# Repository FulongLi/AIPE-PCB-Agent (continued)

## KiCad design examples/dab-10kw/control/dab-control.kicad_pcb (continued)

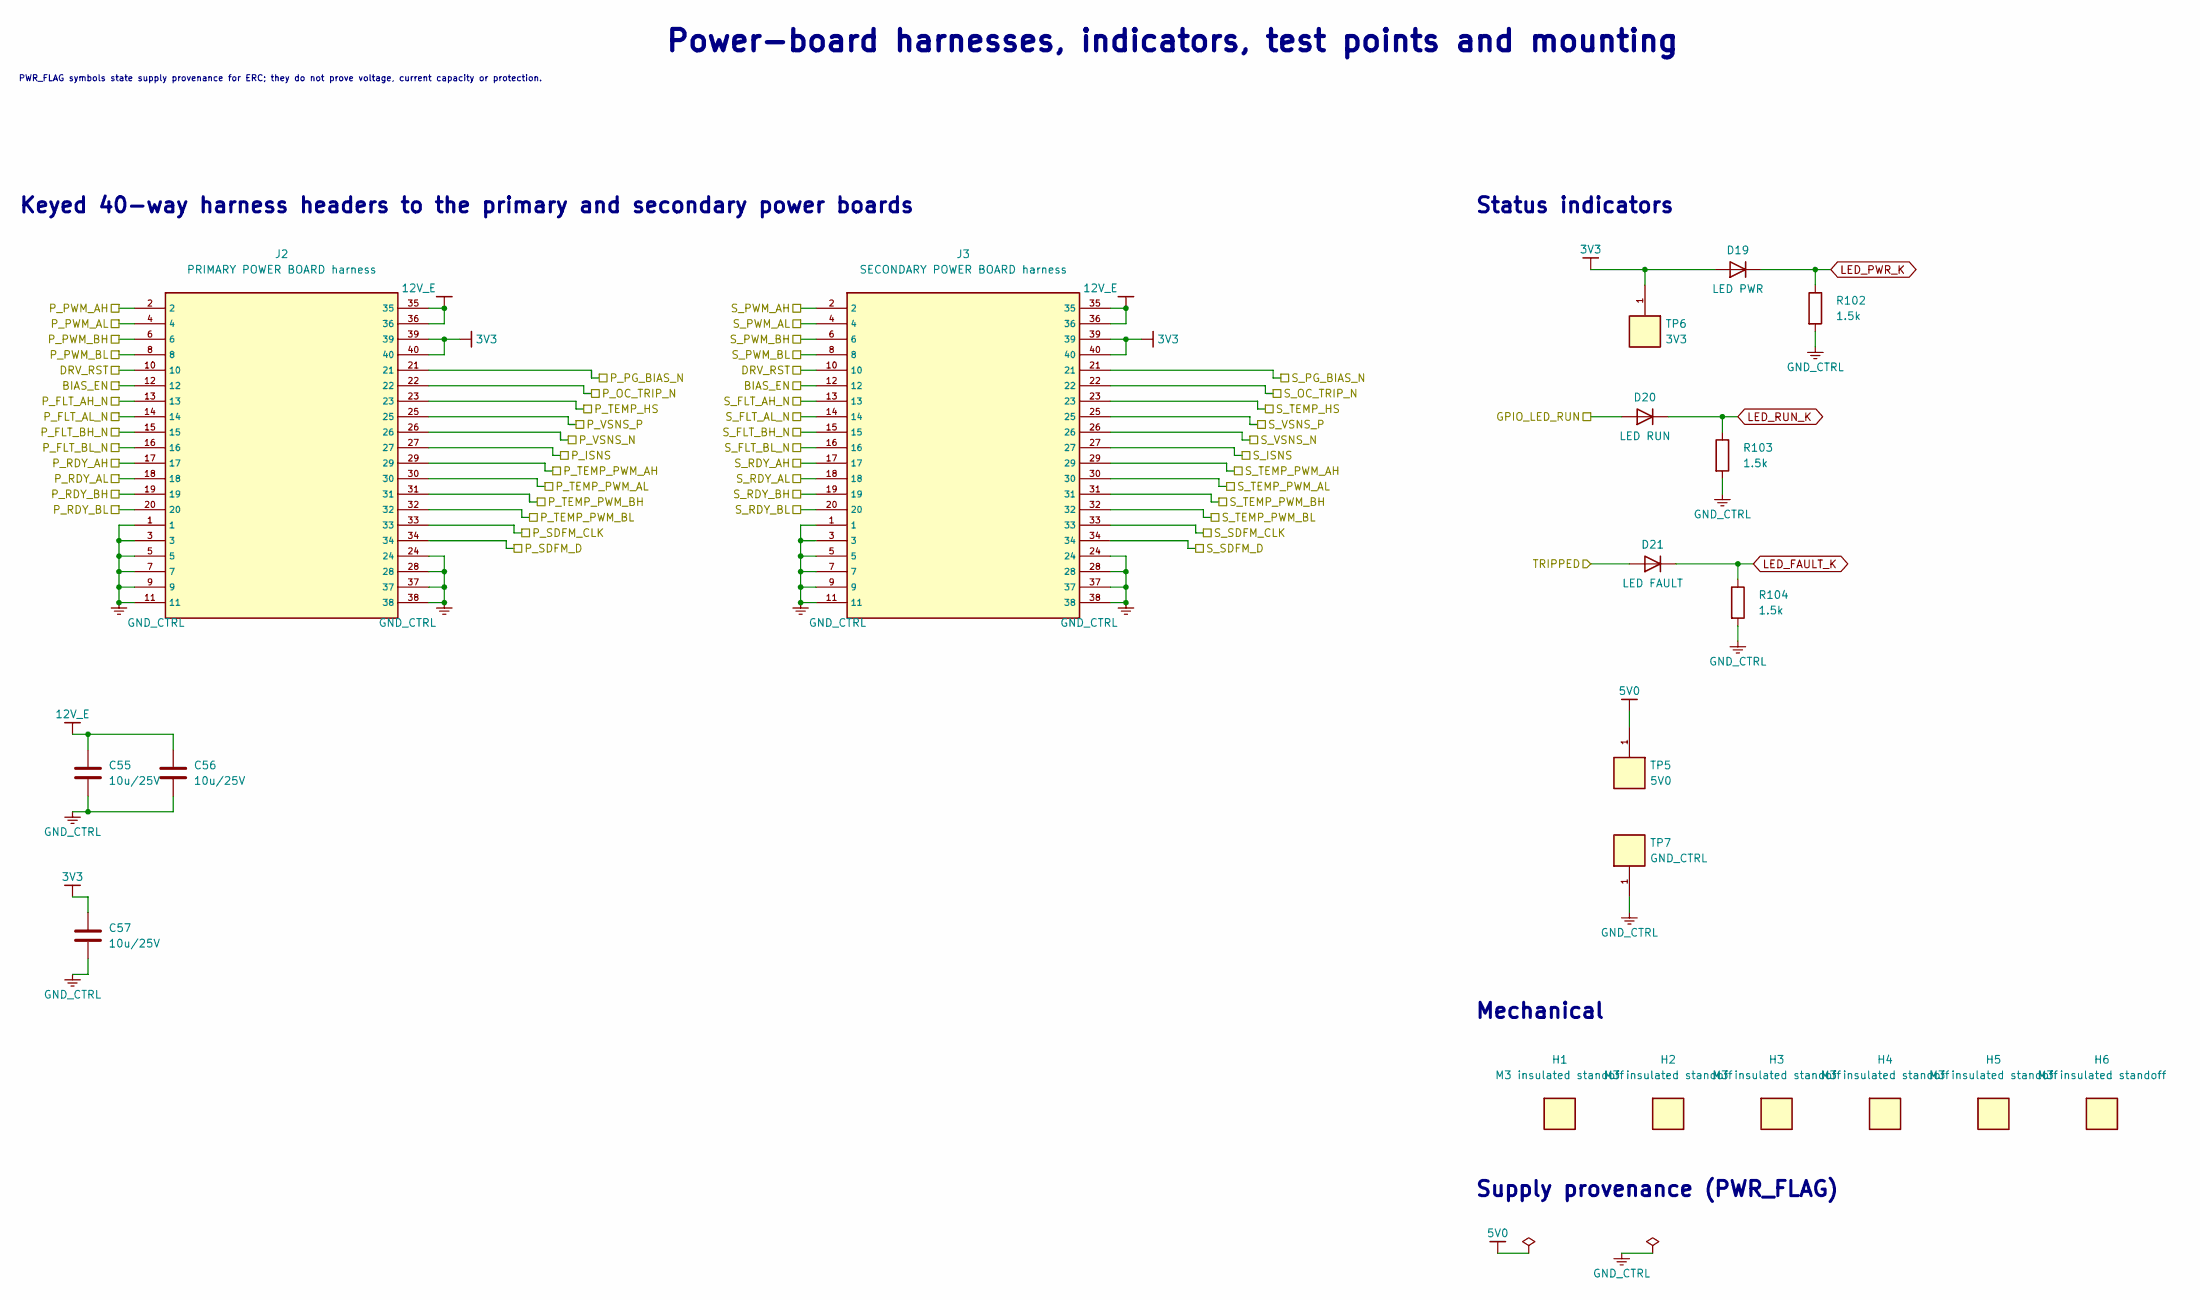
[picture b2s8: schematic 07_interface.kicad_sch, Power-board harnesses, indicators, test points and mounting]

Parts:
C55, C56, C57: 10u/25V; C_1210_3225Metric
D19: LED PWR; LED_0805_2012Metric
D20: LED RUN; LED_0805_2012Metric
D21: LED FAULT; LED_0805_2012Metric
H1, H2, H3, H4, H5, H6: M3 insulated standoff; MountingHole_3.2mm_M3
J2: PRIMARY POWER BOARD harness; IDC-Header_2x20_P2.54mm_Vertical
J3: SECONDARY POWER BOARD harness; IDC-Header_2x20_P2.54mm_Vertical
R102, R103, R104: 1.5k; R_0603_1608Metric
TP5: 5V0; TestPoint_Pad_D1.0mm
TP6: 3V3; TestPoint_Pad_D1.0mm
TP7: GND_CTRL; TestPoint_Pad_D1.0mm

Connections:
3V3: C57.1, D19.2 (A), J2.39, J2.40, J3.39, J3.40, TP6.1; also elsewhere on the board
5V0: TP5.1; also elsewhere on the board
12V_E: C55.1, C56.1, J2.35, J2.36, J3.35, J3.36; also elsewhere on the board
BIAS_EN: J2.12, J3.12; also elsewhere on the board
DRV_RST: J2.10, J3.10; also elsewhere on the board
GND_CTRL: C55.2, C56.2, C57.2, J2.1, J2.3, J2.5, J2.7, J2.9, J2.11, J2.24, J2.28, J2.37, J2.38, J3.1, J3.3, J3.5, J3.7, J3.9, J3.11, J3.24, J3.28, J3.37, J3.38, R102.2, R103.2, R104.2, TP7.1; also elsewhere on the board
GPIO_LED_RUN: D20.2 (A); also elsewhere on the board
LED_FAULT_K: D21.1 (K), R104.1
LED_PWR_K: D19.1 (K), R102.1
LED_RUN_K: D20.1 (K), R103.1
P_FLT_AH_N: J2.13; also elsewhere on the board
P_FLT_AL_N: J2.14; also elsewhere on the board
P_FLT_BH_N: J2.15; also elsewhere on the board
P_FLT_BL_N: J2.16; also elsewhere on the board
P_ISNS: J2.27; also elsewhere on the board
P_OC_TRIP_N: J2.22; also elsewhere on the board
P_PG_BIAS_N: J2.21; also elsewhere on the board
P_PWM_AH: J2.2; also elsewhere on the board
P_PWM_AL: J2.4; also elsewhere on the board
P_PWM_BH: J2.6; also elsewhere on the board
P_PWM_BL: J2.8; also elsewhere on the board
P_RDY_AH: J2.17; also elsewhere on the board
P_RDY_AL: J2.18; also elsewhere on the board
P_RDY_BH: J2.19; also elsewhere on the board
P_RDY_BL: J2.20; also elsewhere on the board
P_SDFM_CLK: J2.33; also elsewhere on the board
P_SDFM_D: J2.34; also elsewhere on the board
P_TEMP_HS: J2.23; also elsewhere on the board
P_TEMP_PWM_AH: J2.29; also elsewhere on the board
P_TEMP_PWM_AL: J2.30; also elsewhere on the board
P_TEMP_PWM_BH: J2.31; also elsewhere on the board
P_TEMP_PWM_BL: J2.32; also elsewhere on the board
P_VSNS_N: J2.26; also elsewhere on the board
P_VSNS_P: J2.25; also elsewhere on the board
S_FLT_AH_N: J3.13; also elsewhere on the board
S_FLT_AL_N: J3.14; also elsewhere on the board
S_FLT_BH_N: J3.15; also elsewhere on the board
S_FLT_BL_N: J3.16; also elsewhere on the board
S_ISNS: J3.27; also elsewhere on the board
S_OC_TRIP_N: J3.22; also elsewhere on the board
S_PG_BIAS_N: J3.21; also elsewhere on the board
S_PWM_AH: J3.2; also elsewhere on the board
S_PWM_AL: J3.4; also elsewhere on the board
S_PWM_BH: J3.6; also elsewhere on the board
S_PWM_BL: J3.8; also elsewhere on the board
S_RDY_AH: J3.17; also elsewhere on the board
S_RDY_AL: J3.18; also elsewhere on the board
S_RDY_BH: J3.19; also elsewhere on the board
S_RDY_BL: J3.20; also elsewhere on the board
S_SDFM_CLK: J3.33; also elsewhere on the board
S_SDFM_D: J3.34; also elsewhere on the board
S_TEMP_HS: J3.23; also elsewhere on the board
S_TEMP_PWM_AH: J3.29; also elsewhere on the board
S_TEMP_PWM_AL: J3.30; also elsewhere on the board
S_TEMP_PWM_BH: J3.31; also elsewhere on the board
S_TEMP_PWM_BL: J3.32; also elsewhere on the board
S_VSNS_N: J3.26; also elsewhere on the board
S_VSNS_P: J3.25; also elsewhere on the board
TRIPPED: D21.2 (A); also elsewhere on the board

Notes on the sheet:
Power-board harnesses, indicators, test points and mounting
PWR_FLAG symbols state supply provenance for ERC; they do not prove voltage, current capacity or protection.
Keyed 40-way harness headers to the primary and secondary power boards
Status indicators
Mechanical
Supply provenance (PWR_FLAG)

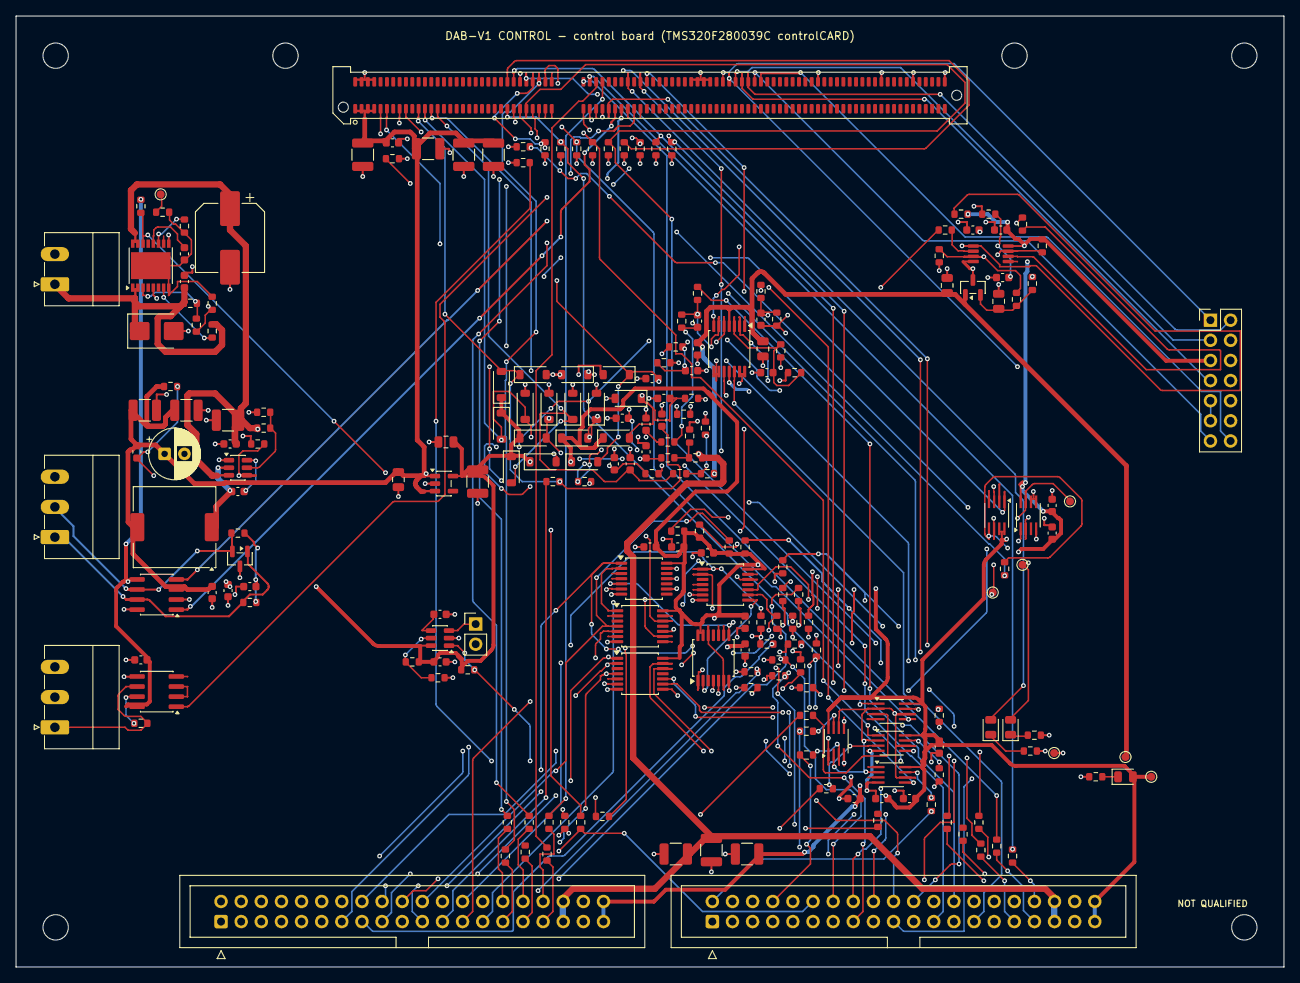
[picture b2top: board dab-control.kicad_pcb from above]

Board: 4 copper layers, 160.0 x 120.0 mm, 224 parts (0 on the bottom side), 165 nets.

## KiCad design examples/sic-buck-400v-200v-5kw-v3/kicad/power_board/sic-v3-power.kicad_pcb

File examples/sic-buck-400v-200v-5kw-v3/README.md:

# V3 — 400 V to 200 V, 5 kW SiC buck

**Engineering prototype review package. CAD VERIFIED; behavioural SIMULATION VERIFIED; HARDWARE VALIDATION PENDING; RELEASE BLOCKED.** Editable design and intended PCB routing are complete. The assembly/process qualifications in the release register remain open; no purchasing, fabrication, energisation or merge is authorized by these files.

Start with the [design review](review/design_review_report.md), [remaining issues](review/remaining_issues.md), [18-issue V2.2 disposition](review/v22_issue_resolution_matrix.md) and [V2.2 comparison](review/v22_vs_v3_comparison.md). The [knowledge audit](review/knowledge_utilisation.md) links sources to decisions and reusable tools.

| Deliverable | Location |
|---|---|
| User requirements, assumptions, baseline and source hashes | `requirements/` |
| Architecture alternatives and selection | `architecture/` |
| Electrical calculations and operating corners | `calculations/`, reproducible `automation/sic_v3/calculations.py` |
| Parts and off-board assembly BOM | `components/`, exact circuit records in `design/circuit_*.json` |
| Native projects | `kicad/power_board/sic-v3-power.kicad_pro`, `kicad/control_board/sic-v3-control.kicad_pro`, `kicad/system_wiring/sic-v3-system.kicad_pro` |
| Schematics | [Power, 9 pages](review/schematic_power.pdf), [control, 9 pages](review/schematic_control.pdf), [system wiring, 5 pages](review/schematic_system.pdf) |
| Independent floorplans and final copper review | `pcb/floorplan_candidates/`, `pcb/routing_analysis/` |
| Simulation decks, logs, data and model limits | `simulation/` |
| F28335 executed reference and implementation specification | `firmware/implementation_specification.md`, `automation/sic_v3/simulation.py` |
| Mechanical envelope, supports, thermal fixture, harness and STEP | `mechanical/` |
| Gerber/drill/BOM/placements/STEP/native export manifests | `manufacturing/power/`, `manufacturing/control/` |
| PCB layout and assembly PDFs, 2D/3D views | `review/pcb_*.pdf`, `review/assembly_*.pdf`, PNGs below |
| Native and independent checks | `verification/`, final gate summary `verification/final_validation.json` |
| Frozen review content hashes and reproduction | `review/package_manifest.json`, [reproduce.md](review/reproduce.md) |

Power: 250 × 180 mm, four 70 µm copper layers, 202 footprints. Control: 160 × 120 mm, four 35 µm layers, 266 footprints. Both have zero native DRC findings, unintended opens and schematic-parity differences under the recorded rule configuration. Three native schematic projects have zero ERC findings. Native CAD success does not establish hardware safety/performance.

Historical designs are unchanged at baseline `20e96fdfa5ea76649daa416ee70b7ea7798a319d`. V3 is larger than V2.2 and does not claim better measured efficiency, EMI, switching stress or transient performance. No software was installed for this task.

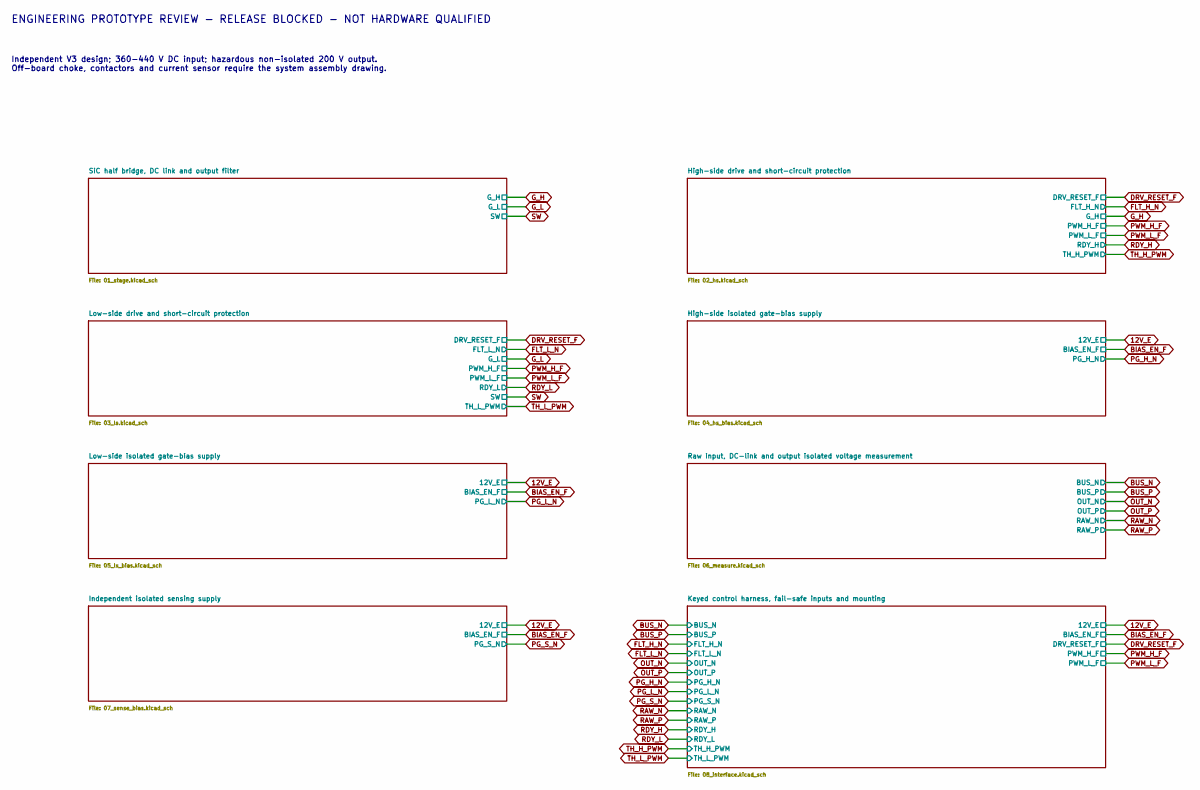
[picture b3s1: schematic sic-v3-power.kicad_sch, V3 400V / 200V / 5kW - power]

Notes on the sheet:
ENGINEERING PROTOTYPE REVIEW - RELEASE BLOCKED - NOT HARDWARE QUALIFIED
Independent V3 design; 360-440 V DC input; hazardous non-isolated 200 V output. Off-board choke, contactors and current sensor require the system assembly drawing.

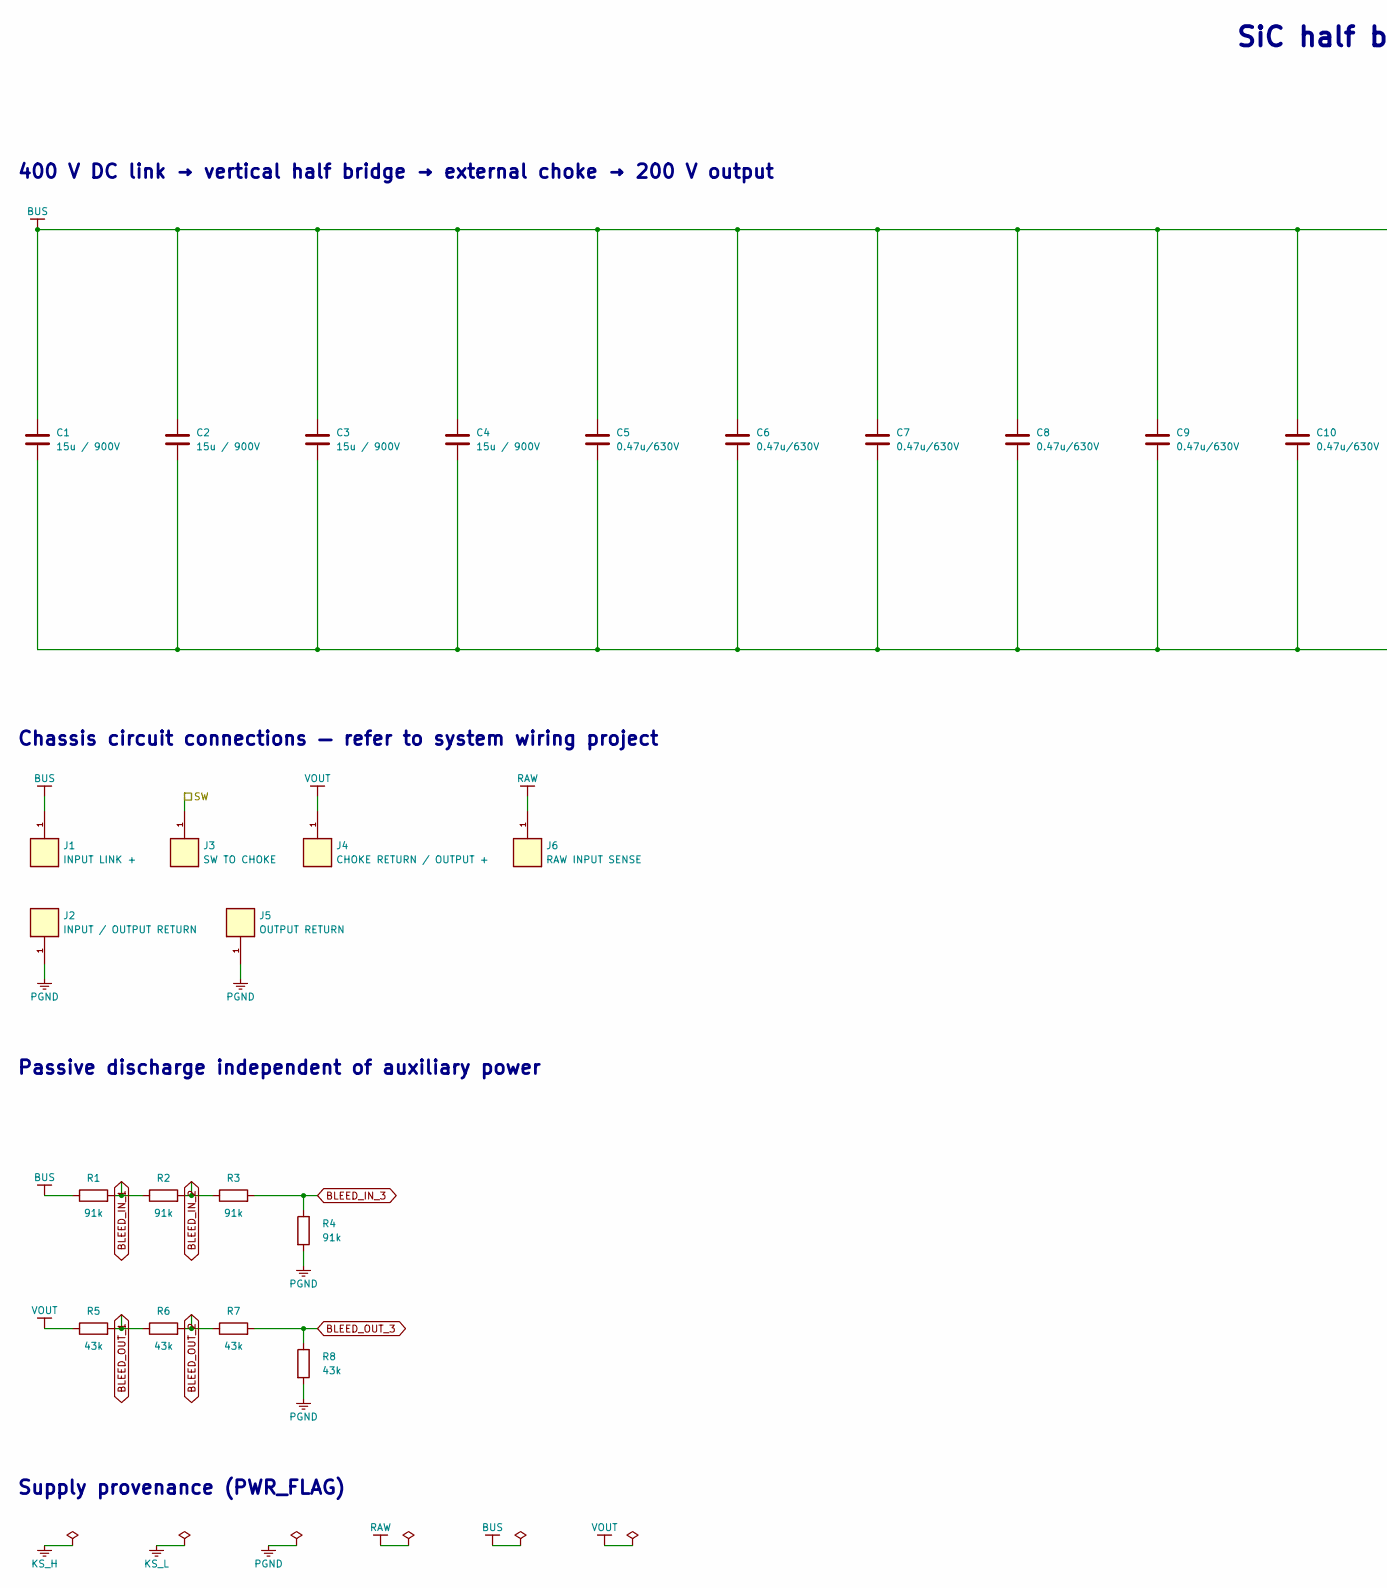
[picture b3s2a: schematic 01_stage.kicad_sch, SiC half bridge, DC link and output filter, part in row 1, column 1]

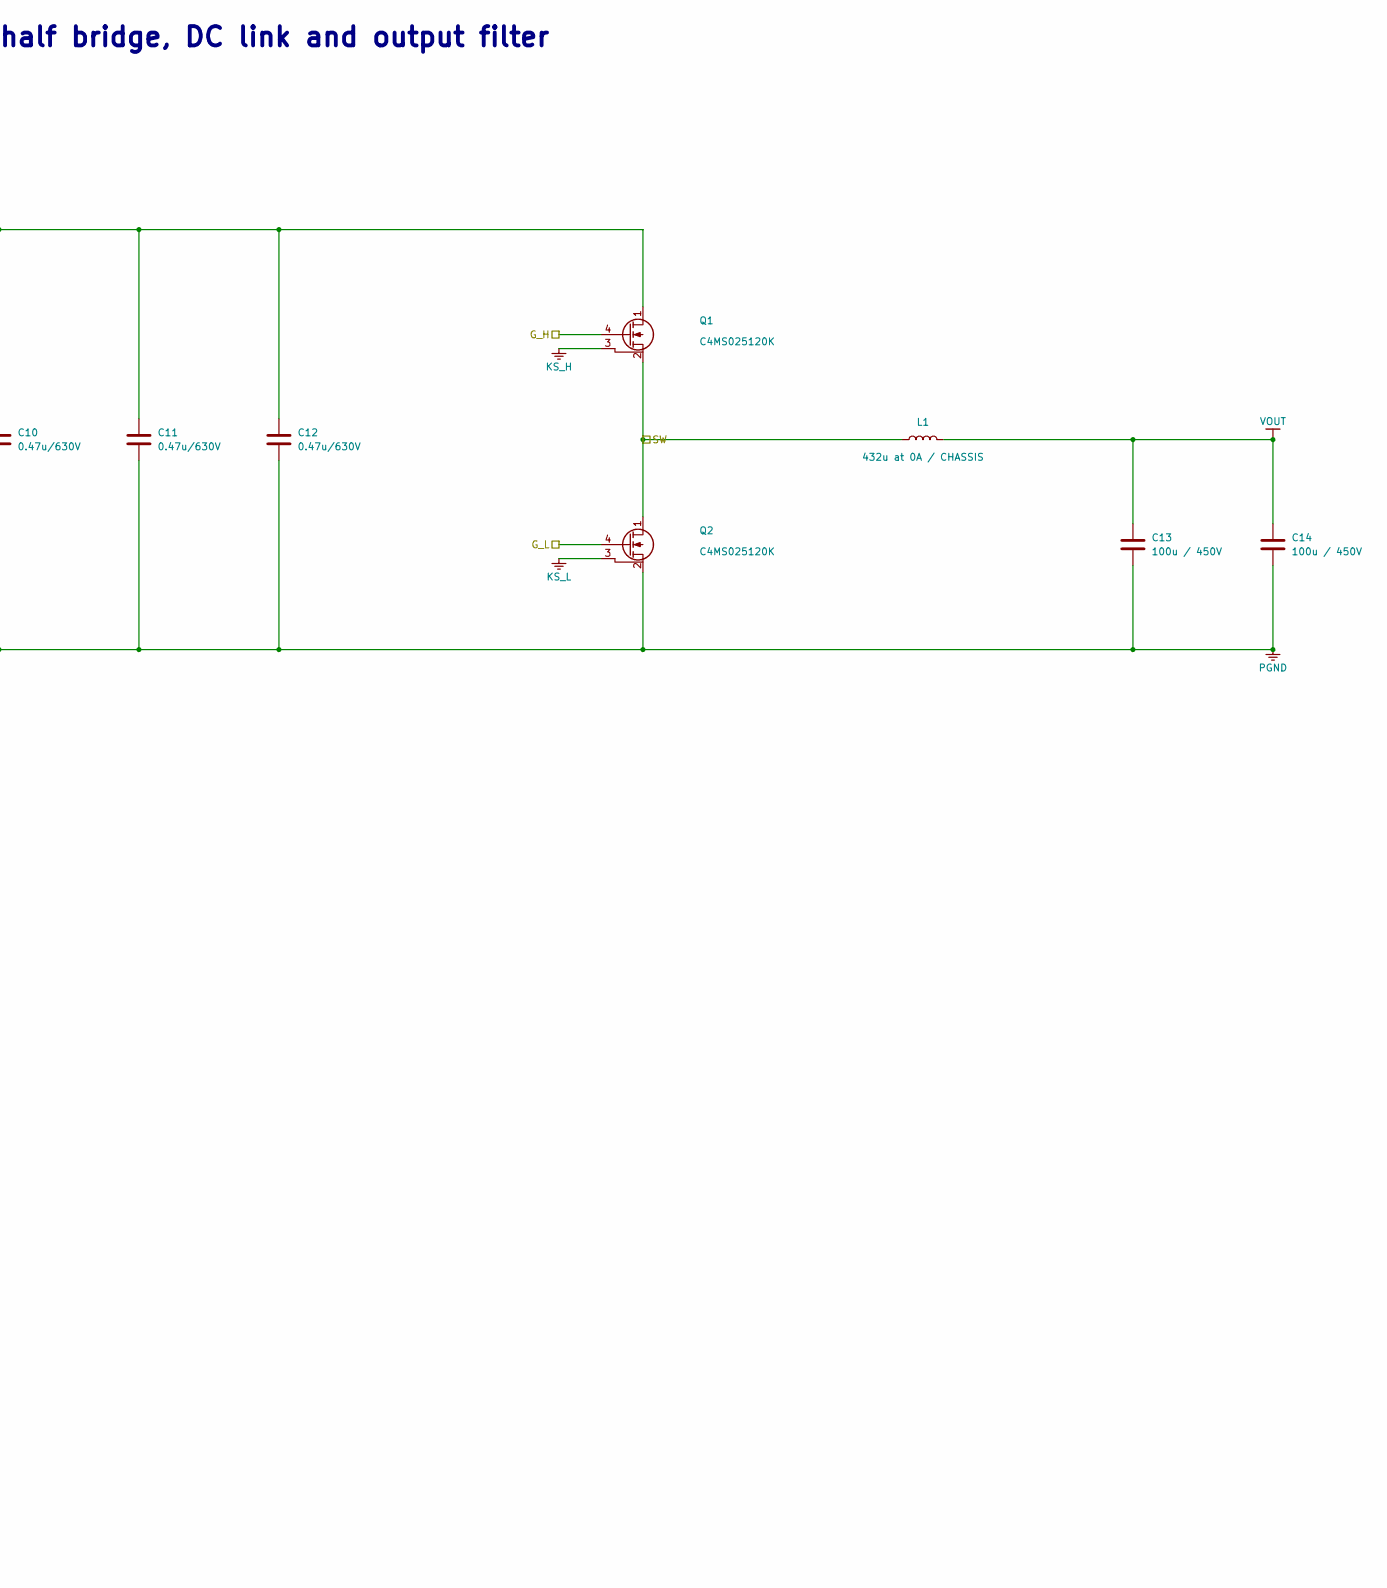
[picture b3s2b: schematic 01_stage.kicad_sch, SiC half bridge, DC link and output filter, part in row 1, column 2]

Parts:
C1, C2, C3, C4: 15u / 900V; V3_CIN_15U
C5, C6, C7, C8, C9, C10, C11, C12: 0.47u/630V; C_2220_5750Metric
C13, C14: 100u / 450V; V3_COUT_100U
J1: INPUT LINK +; Wuerth_REDCUBE-THR_WP-THRSH_74651195_THR
J2: INPUT / OUTPUT RETURN; Wuerth_REDCUBE-THR_WP-THRSH_74651195_THR
J3: SW TO CHOKE; Wuerth_REDCUBE-THR_WP-THRSH_74651195_THR
J4: CHOKE RETURN / OUTPUT +; Wuerth_REDCUBE-THR_WP-THRSH_74651195_THR
J5: OUTPUT RETURN; Wuerth_REDCUBE-THR_WP-THRSH_74651195_THR
J6: RAW INPUT SENSE; Wuerth_REDCUBE-THR_WP-THRSH_74651195_THR
L1: 432u at 0A / CHASSIS
Q1, Q2: C4MS025120K; V3_TO247_4
R1, R2, R3, R4: 91k; R_2512_6332Metric
R5, R6, R7, R8: 43k; R_2512_6332Metric

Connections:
BLEED_IN_1: R1.2, R2.1
BLEED_IN_2: R2.2, R3.1
BLEED_IN_3: R3.2, R4.1
BLEED_OUT_1: R5.2, R6.1
BLEED_OUT_2: R6.2, R7.1
BLEED_OUT_3: R7.2, R8.1
BUS: C1.1, C2.1, C3.1, C4.1, C5.1, C6.1, C7.1, C8.1, C9.1, C10.1, C11.1, C12.1, J1.1, Q1.1 (D), R1.1; also elsewhere on the board
G_H: Q1.4 (G); also elsewhere on the board
G_L: Q2.4 (G); also elsewhere on the board
KS_H: Q1.3 (KS); also elsewhere on the board
KS_L: Q2.3 (KS); also elsewhere on the board
PGND: C1.2, C2.2, C3.2, C4.2, C5.2, C6.2, C7.2, C8.2, C9.2, C10.2, C11.2, C12.2, C13.2, C14.2, J2.1, J5.1, Q2.2 (S), R4.2, R8.2; also elsewhere on the board
RAW: J6.1; also elsewhere on the board
SW: J3.1, L1.1, Q1.2 (S), Q2.1 (D); also elsewhere on the board
VOUT: C13.1, C14.1, J4.1, L1.2, R5.1; also elsewhere on the board

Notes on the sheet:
SiC half bridge, DC link and output filter
400 V DC link → vertical half bridge → external choke → 200 V output
Chassis circuit connections — refer to system wiring project
Passive discharge independent of auxiliary power
Supply provenance (PWR_FLAG)

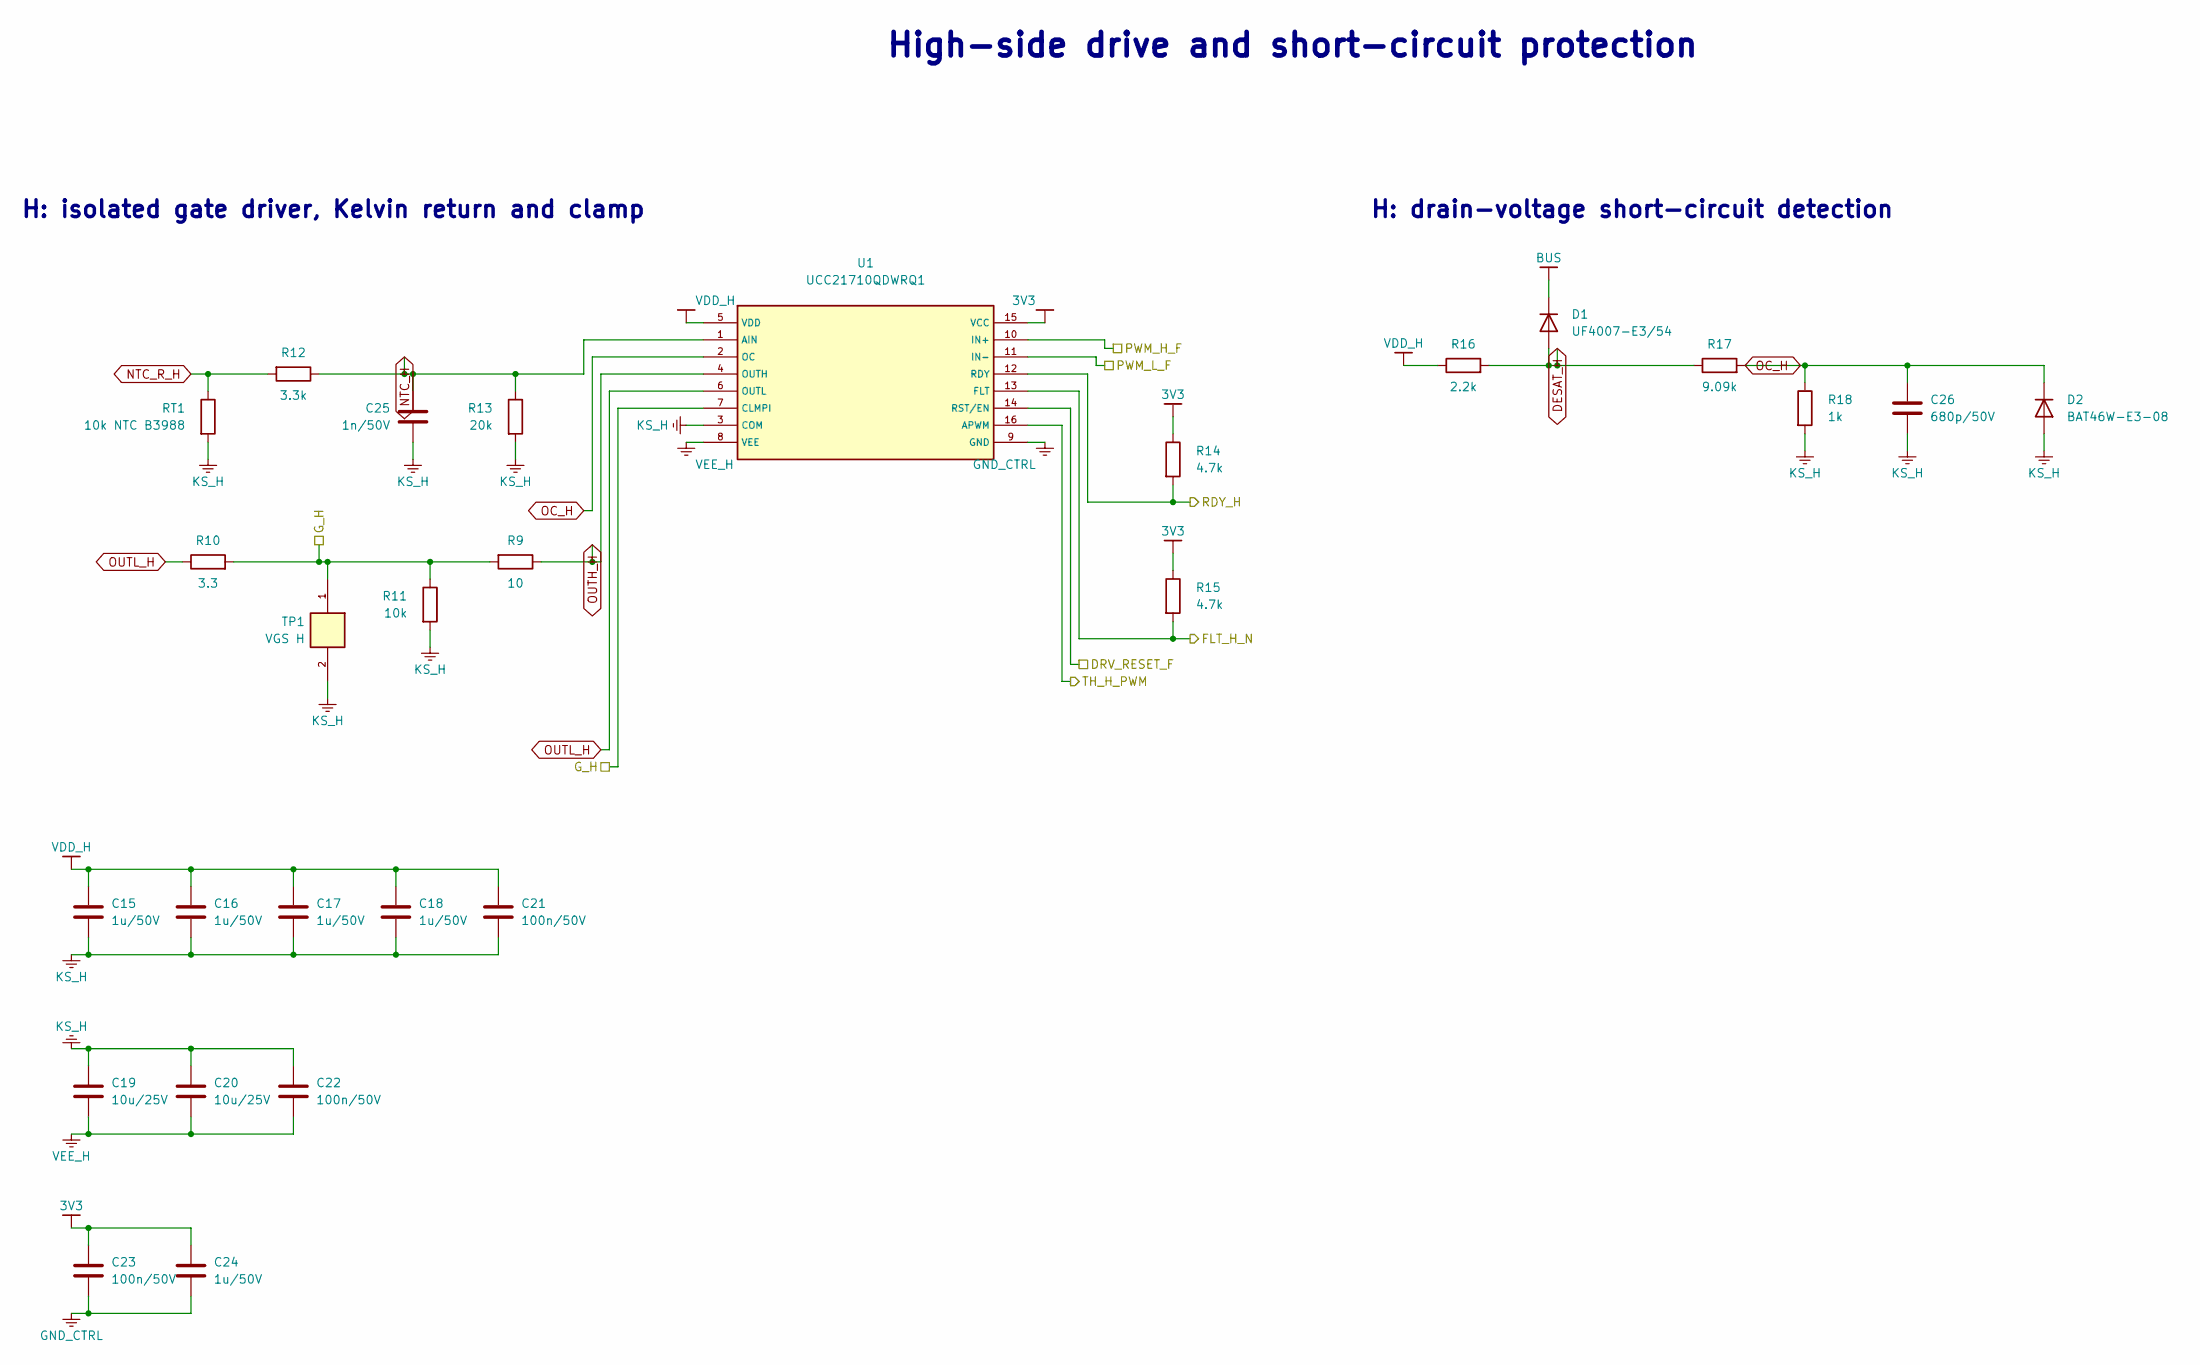
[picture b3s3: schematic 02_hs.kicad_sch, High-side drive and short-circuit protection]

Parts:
C15, C16, C17, C18, C24: 1u/50V; C_0805_2012Metric
C19, C20: 10u/25V; C_1210_3225Metric
C21, C22, C23: 100n/50V; C_0603_1608Metric
C25: 1n/50V; C_0603_1608Metric
C26: 680p/50V; C_0603_1608Metric
D1: UF4007-E3/54; D_DO-41_SOD81_P10.16mm_Horizontal
D2: BAT46W-E3-08; D_SOD-123
R9: 10; R_1206_3216Metric
R10: 3.3; R_1206_3216Metric
R11: 10k; R_0805_2012Metric
R12: 3.3k; R_0603_1608Metric
R13: 20k; R_0603_1608Metric
R14, R15: 4.7k; R_0603_1608Metric
R16: 2.2k; R_1206_3216Metric
R17: 9.09k; R_0603_1608Metric
R18: 1k; R_0603_1608Metric
RT1: 10k NTC B3988; R_0805_2012Metric
TP1: VGS H; TestPoint_2Pads_Pitch2.54mm_Drill0.8mm
U1: UCC21710QDWRQ1; V3_UCC21710_HV

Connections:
3V3: C23.1, C24.1, R14.1, R15.1, U1.15 (VCC); also elsewhere on the board
BUS: D1.1 (K); also elsewhere on the board
DESAT_H: D1.2 (A), R16.2, R17.1
DRV_RESET_F: U1.14 (RST/EN); also elsewhere on the board
FLT_H_N: R15.2, U1.13 (FLT); also elsewhere on the board
GND_CTRL: C23.2, C24.2, U1.9 (GND); also elsewhere on the board
G_H: R9.2, R10.2, R11.1, TP1.1, U1.7 (CLMPI); also elsewhere on the board
KS_H: C15.2, C16.2, C17.2, C18.2, C19.1, C20.1, C21.2, C22.1, C25.2, C26.2, D2.2 (A), R11.2, R13.2, R18.2, RT1.2, TP1.2, U1.3 (COM); also elsewhere on the board
NTC_H: C25.1, R12.1, R13.1, U1.1 (AIN)
NTC_R_H: R12.2, RT1.1
OC_H: C26.1, D2.1 (K), R17.2, R18.1, U1.2 (OC)
OUTH_H: R9.1, U1.4 (OUTH)
OUTL_H: R10.1, U1.6 (OUTL)
PWM_H_F: U1.10 (IN+); also elsewhere on the board
PWM_L_F: U1.11 (IN-); also elsewhere on the board
RDY_H: R14.2, U1.12 (RDY); also elsewhere on the board
TH_H_PWM: U1.16 (APWM); also elsewhere on the board
VDD_H: C15.1, C16.1, C17.1, C18.1, C21.1, R16.1, U1.5 (VDD); also elsewhere on the board
VEE_H: C19.2, C20.2, C22.2, U1.8 (VEE); also elsewhere on the board

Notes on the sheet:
High-side drive and short-circuit protection
H: isolated gate driver, Kelvin return and clamp
H: drain-voltage short-circuit detection

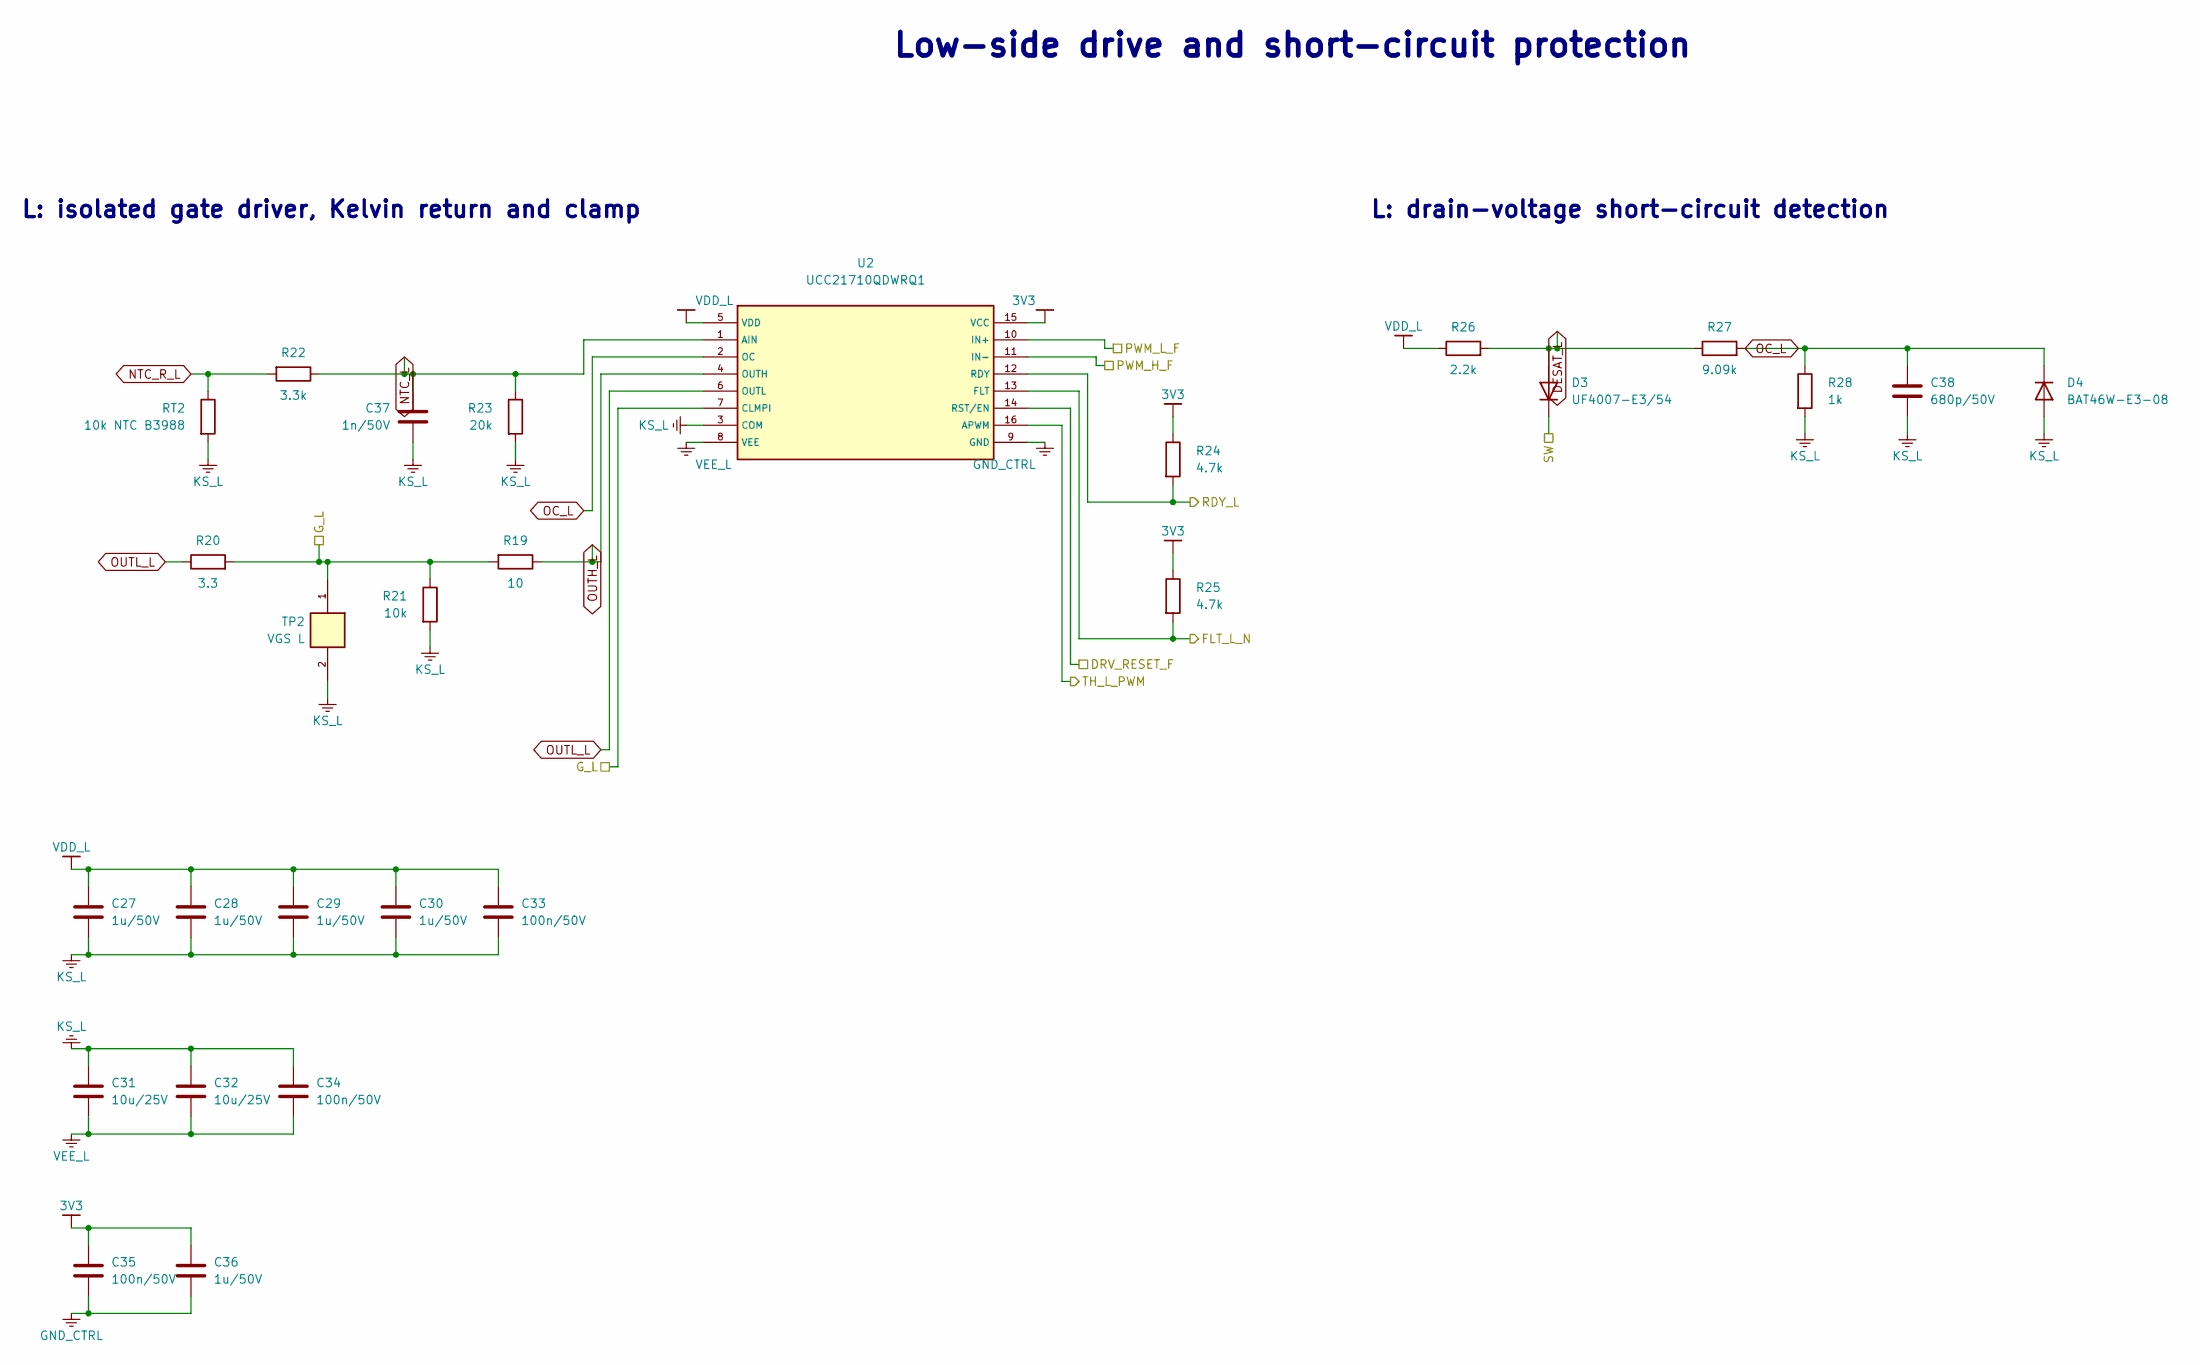
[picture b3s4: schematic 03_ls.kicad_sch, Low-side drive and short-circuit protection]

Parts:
C27, C28, C29, C30, C36: 1u/50V; C_0805_2012Metric
C31, C32: 10u/25V; C_1210_3225Metric
C33, C34, C35: 100n/50V; C_0603_1608Metric
C37: 1n/50V; C_0603_1608Metric
C38: 680p/50V; C_0603_1608Metric
D3: UF4007-E3/54; D_DO-41_SOD81_P10.16mm_Horizontal
D4: BAT46W-E3-08; D_SOD-123
R19: 10; R_1206_3216Metric
R20: 3.3; R_1206_3216Metric
R21: 10k; R_0805_2012Metric
R22: 3.3k; R_0603_1608Metric
R23: 20k; R_0603_1608Metric
R24, R25: 4.7k; R_0603_1608Metric
R26: 2.2k; R_1206_3216Metric
R27: 9.09k; R_0603_1608Metric
R28: 1k; R_0603_1608Metric
RT2: 10k NTC B3988; R_0805_2012Metric
TP2: VGS L; TestPoint_2Pads_Pitch2.54mm_Drill0.8mm
U2: UCC21710QDWRQ1; V3_UCC21710_HV

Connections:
3V3: C35.1, C36.1, R24.1, R25.1, U2.15 (VCC); also elsewhere on the board
DESAT_L: D3.2 (A), R26.2, R27.1
DRV_RESET_F: U2.14 (RST/EN); also elsewhere on the board
FLT_L_N: R25.2, U2.13 (FLT); also elsewhere on the board
GND_CTRL: C35.2, C36.2, U2.9 (GND); also elsewhere on the board
G_L: R19.2, R20.2, R21.1, TP2.1, U2.7 (CLMPI); also elsewhere on the board
KS_L: C27.2, C28.2, C29.2, C30.2, C31.1, C32.1, C33.2, C34.1, C37.2, C38.2, D4.2 (A), R21.2, R23.2, R28.2, RT2.2, TP2.2, U2.3 (COM); also elsewhere on the board
NTC_L: C37.1, R22.1, R23.1, U2.1 (AIN)
NTC_R_L: R22.2, RT2.1
OC_L: C38.1, D4.1 (K), R27.2, R28.1, U2.2 (OC)
OUTH_L: R19.1, U2.4 (OUTH)
OUTL_L: R20.1, U2.6 (OUTL)
PWM_H_F: U2.11 (IN-); also elsewhere on the board
PWM_L_F: U2.10 (IN+); also elsewhere on the board
RDY_L: R24.2, U2.12 (RDY); also elsewhere on the board
SW: D3.1 (K); also elsewhere on the board
TH_L_PWM: U2.16 (APWM); also elsewhere on the board
VDD_L: C27.1, C28.1, C29.1, C30.1, C33.1, R26.1, U2.5 (VDD); also elsewhere on the board
VEE_L: C31.2, C32.2, C34.2, U2.8 (VEE); also elsewhere on the board

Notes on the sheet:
Low-side drive and short-circuit protection
L: isolated gate driver, Kelvin return and clamp
L: drain-voltage short-circuit detection
